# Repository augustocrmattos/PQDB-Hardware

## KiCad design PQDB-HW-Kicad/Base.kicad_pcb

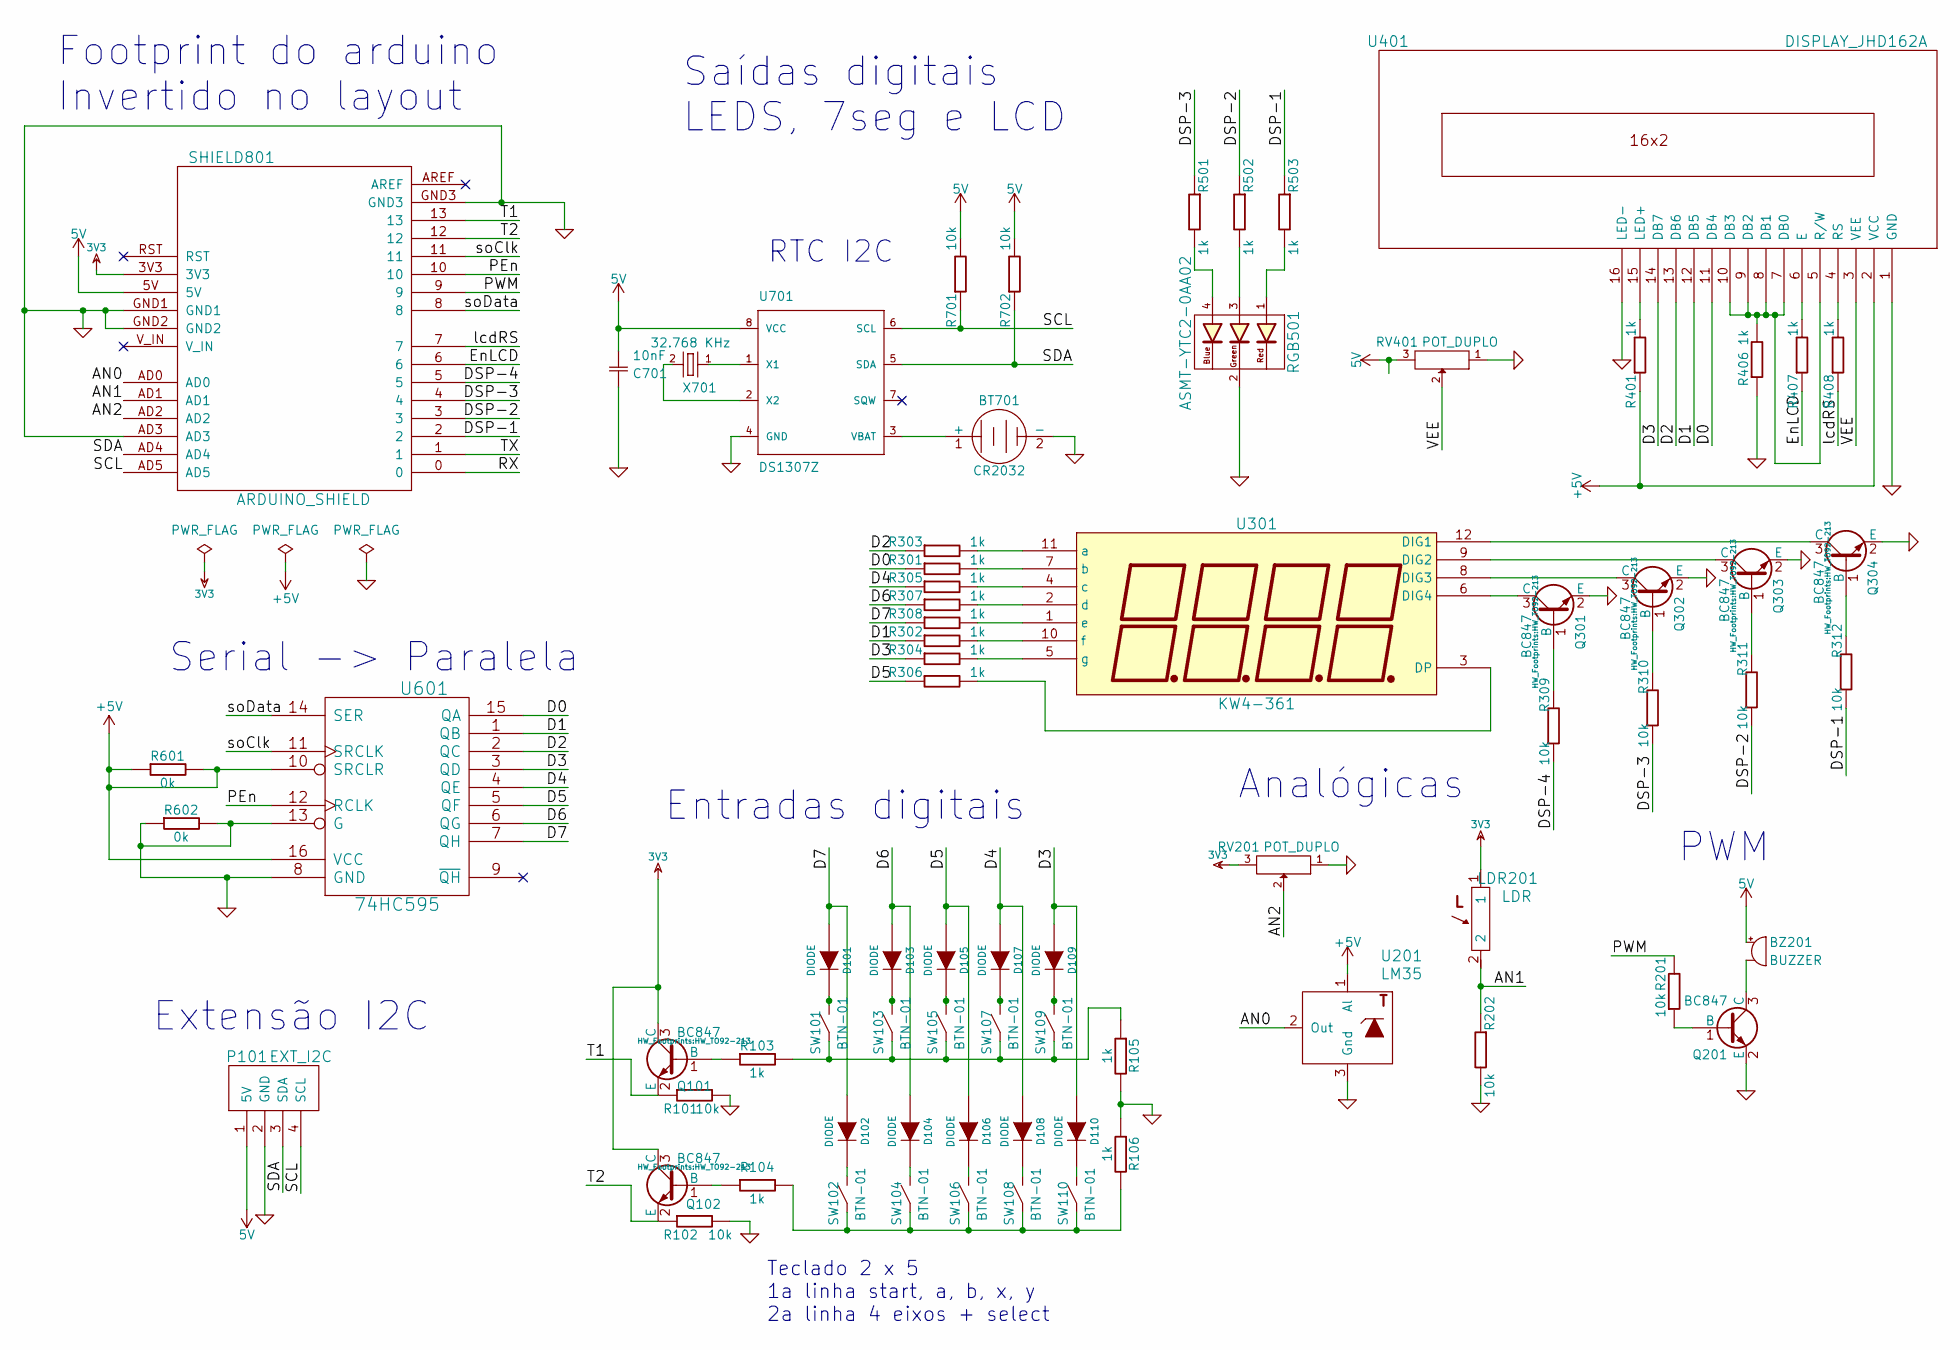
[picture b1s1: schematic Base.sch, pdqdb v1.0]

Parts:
BT701: CR2032; HW_CR2032H
BZ201: BUZZER; HW_Buzzer
C701: 10nF; HW_CAPACITOR
D101, D102, D103, D104, D105, D106, D107, D108, D109, D110: DIODE; D5
LDR201: LDR; HW_LDR
P101: EXT_I2C
Q101, Q102, Q201, Q301, Q302, Q303, Q304: BC847; HW_TO92-213
R101, R102, R201, R202, R309, R310, R311, R312, R701, R702: 10k; HW_Resistor
R103, R104, R105, R106, R301, R302, R303, R304, R305, R306, R307, R308, R401, R406, R407, R408, R501, R502, R503: 1k; HW_Resistor
R601, R602: 0k; Resistor_Horizontal_RM15mm
RGB501: ASMT-YTC2-0AA02; LED-5MM
RV201, RV401: POT_DUPLO; HW_Potenciometro_2_Duplo
SHIELD801: ARDUINO_SHIELD; ARDUINO_SHIELD_2
SW101, SW102, SW103, SW104, SW105, SW106, SW107, SW108, SW109, SW110: BTN-01; HW_Switch_tactil_adaptada
U201: LM35; TO-92_Molded_Narrow_Reverse
U301: KW4-361; HW_Disp_7seg_4dig
U401: DISPLAY_JHD162A; HW_LCD
U601: 74HC595; HW_DIP-16__300_ELL
U701: DS1307Z; DIP-8_W7.62mm_LongPads
X701: 32.768 KHz; Crystal_Round_Horizontal_2mm

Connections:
3V3: LDR201.1, Q101.3 (C), Q102.3 (C), RV201.3, SHIELD801.3V3
/AN0: SHIELD801.AD0, U201.2 (Out)
/AN1: LDR201.2, R202.1, SHIELD801.AD1
/AN2: RV201.2, SHIELD801.AD2
/D0: R301.1, U401.11 (DB4), U601.15 (QA)
/D1: R302.1, U401.12 (DB5), U601.1 (QB)
/D2: R303.1, U401.13 (DB6), U601.2 (QC)
/D3: D109.1 (A), D110.1 (A), R304.1, U401.14 (DB7), U601.3 (QD)
/D4: D107.1 (A), D108.1 (A), R305.1, U601.4 (QE)
/D5: D105.1 (A), D106.1 (A), R306.1, U601.5 (QF)
/D6: D103.1 (A), D104.1 (A), R307.1, U601.6 (QG)
/D7: D101.1 (A), D102.1 (A), R308.1, U601.7 (QH)
/DSP-1: R312.1, R503.1, SHIELD801.2
/DSP-2: R311.1, R502.1, SHIELD801.3
/DSP-3: R310.1, R501.1, SHIELD801.4
/DSP-4: R309.1, SHIELD801.5
/EnLCD: R407.1, SHIELD801.6
/PEn: SHIELD801.10, U601.12 (RCLK)
/PWM: R201.2, SHIELD801.9
/RX: SHIELD801.0
/SCL: P101.4 (SCL), R701.1, SHIELD801.AD5, U701.6 (SCL)
/SDA: P101.3 (SDA), R702.1, SHIELD801.AD4, U701.5 (SDA)
/T1: Q101.2 (E), R101.1, SHIELD801.13
/T2: Q102.2 (E), R102.1, SHIELD801.12
/TX: SHIELD801.1
/VEE: RV401.2, U401.3 (VEE)
/lcdRS: R408.1, SHIELD801.7
/soClk: SHIELD801.11, U601.11 (SRCLK)
/soData: SHIELD801.8, U601.14 (SER)
GND: BT701.2 (-), C701.1, P101.2 (GND), Q201.2 (E), Q301.2 (E), Q302.2 (E), Q303.2 (E), Q304.2 (E), R101.2, R102.2, R105.2, R106.1, R202.2, R406.1, R602.1, R602.2, RGB501.2 (KG), RV201.1, RV401.1, SHIELD801.AD3, SHIELD801.GND1, SHIELD801.GND2, SHIELD801.GND3, U201.3 (Gnd), U401.1 (GND), U401.16 (LED-), U601.8 (GND), U601.13 (G), U701.4 (GND)
unnamed: BT701.1 (+), U701.3 (VBAT)
unnamed: BZ201.2, Q201.3 (C)
unnamed: D101.2 (K), SW101.2
unnamed: D102.2 (K), SW102.2
unnamed: D103.2 (K), SW103.2
unnamed: D104.2 (K), SW104.2
unnamed: D105.2 (K), SW105.2
unnamed: D106.2 (K), SW106.2
unnamed: D107.2 (K), SW107.2
unnamed: D108.2 (K), SW108.2
unnamed: D109.2 (K), SW109.2
unnamed: D110.2 (K), SW110.2
unnamed: Q101.1 (B), R103.1
unnamed: Q102.1 (B), R104.1
unnamed: Q201.1 (B), R201.1
unnamed: Q301.1 (B), R309.2
unnamed: Q301.3 (C), U301.6 (DIG4)
unnamed: Q302.1 (B), R310.2
unnamed: Q302.3 (C), U301.8 (DIG3)
unnamed: Q303.1 (B), R311.2
unnamed: Q303.3 (C), U301.9 (DIG2)
unnamed: Q304.1 (B), R312.2
unnamed: Q304.3 (C), U301.12 (DIG1)
unnamed: R103.2, R105.1, SW101.1, SW103.1, SW105.1, SW107.1, SW109.1
unnamed: R104.2, R106.2, SW102.1, SW104.1, SW106.1, SW108.1, SW110.1
unnamed: R301.2, U301.7 (b)
unnamed: R302.2, U301.10 (f)
unnamed: R303.2, U301.11 (a)
unnamed: R304.2, U301.5 (g)
unnamed: R305.2, U301.4 (c)
unnamed: R306.2, U301.3 (DP)
unnamed: R307.2, U301.2 (d)
unnamed: R308.2, U301.1 (e)
unnamed: R401.2, U401.15 (LED+)
unnamed: R406.2, U401.5 (R/W), U401.7 (DB0), U401.8 (DB1), U401.9 (DB2), U401.10 (DB3)
unnamed: R407.2, U401.6 (E)
unnamed: R408.2, U401.4 (RS)
unnamed: R501.2, RGB501.4 (AB)
unnamed: R502.2, RGB501.3 (AG)
unnamed: R503.2, RGB501.1 (AR)
unnamed: U701.1 (X1), X701.1
unnamed: U701.2 (X2), X701.2

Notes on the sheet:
RTC I2C
Saídas digitais LEDS, 7seg e LCD
Teclado 2 x 5 1a linha start, a, b, x, y 2a linha 4 eixos + select
Analógicas
PWM
Serial -> Paralela
Footprint do arduino Invertido no layout
Entradas digitais
Extensão I2C

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
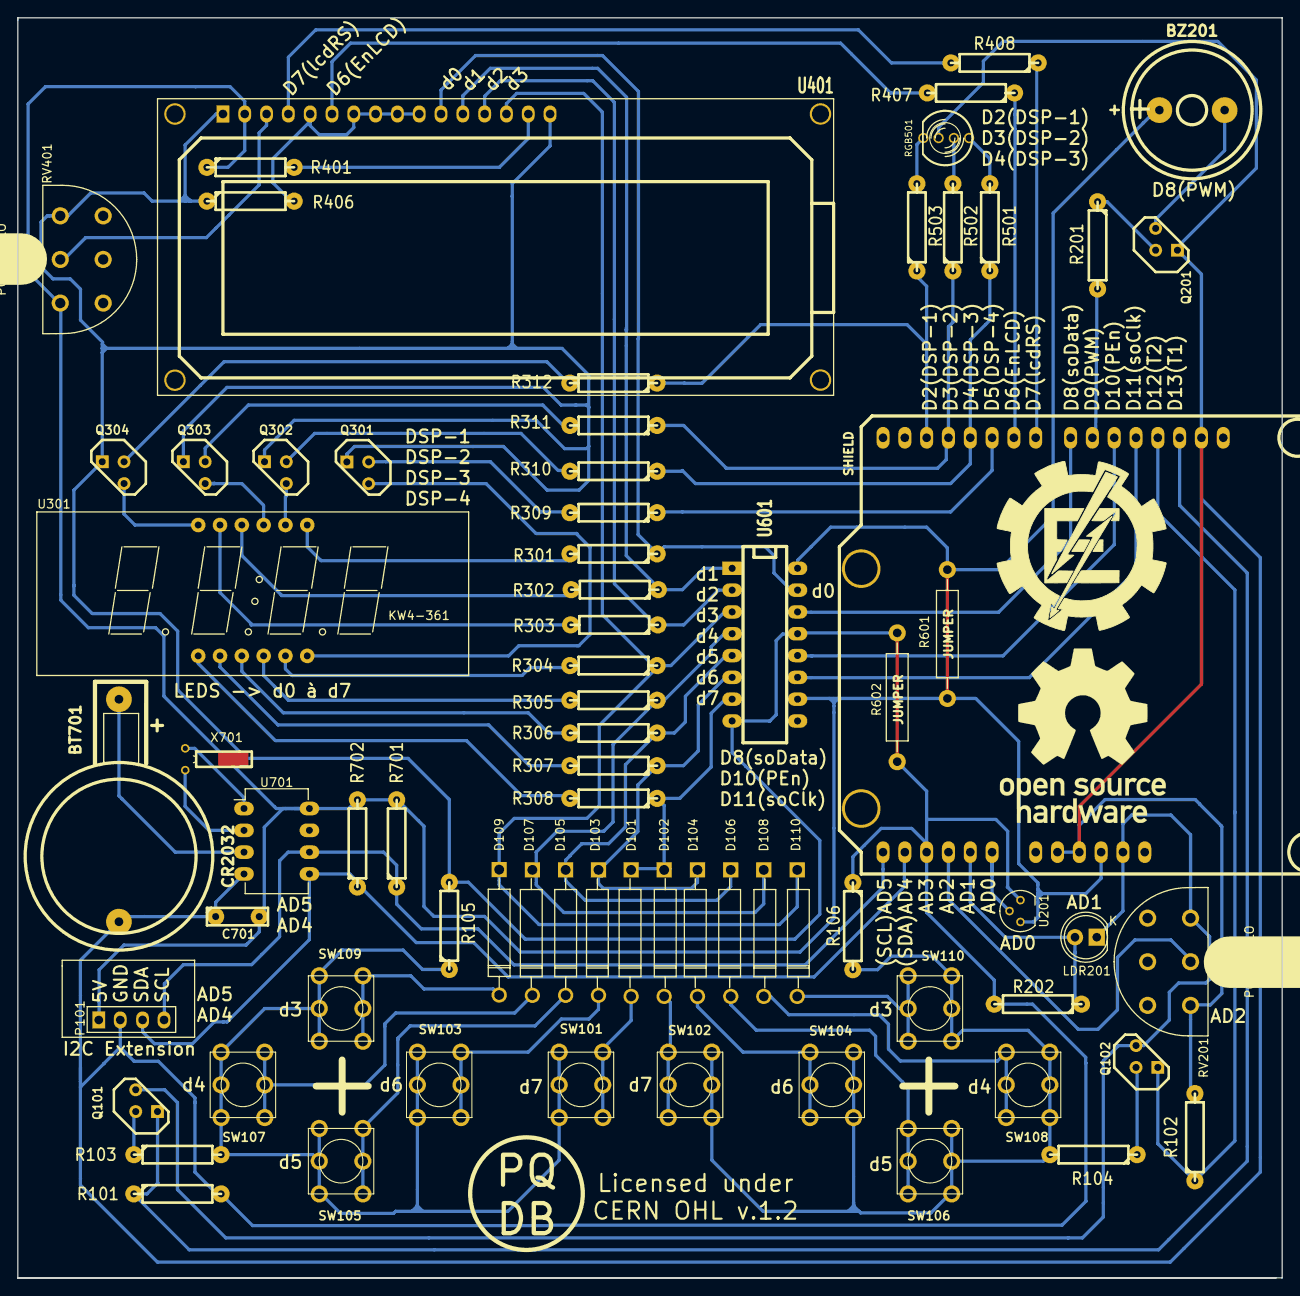
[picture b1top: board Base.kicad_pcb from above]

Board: 2 copper layers, 147.2 x 146.8 mm, 73 parts (1 on the bottom side), 71 nets.

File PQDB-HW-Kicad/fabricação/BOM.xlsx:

Reference | Value | Footprint
R312 | Resistor 1/8W 10K PTH | CR25
R201 | Resistor 1/8W 10K PTH | CR25
R311 | Resistor 1/8W 10K PTH | CR25
R310 | Resistor 1/8W 10K PTH | CR25
R309 | Resistor 1/8W 10K PTH | CR25
R202 | Resistor 1/8W 10K PTH | CR25
R102 | Resistor 1/8W 10K PTH | CR25
R701 | Resistor 1/8W 10K PTH | CR25
R702 | Resistor 1/8W 10K PTH | CR25
R101 | Resistor 1/8W 10K PTH | CR25
C701 | Capacitor cerâmico 25V 10nF PTH | 5mm
R407 | Resistor 1/8W 1K PTH | CR25
R408 | Resistor 1/8W 1K PTH | CR25
R406 | Resistor 1/8W 1K PTH | CR25
R304 | Resistor 1/8W 1K PTH | CR25
R303 | Resistor 1/8W 1K PTH | CR25
R302 | Resistor 1/8W 1K PTH | CR25
R301 | Resistor 1/8W 1K PTH | CR25
R308 | Resistor 1/8W 1K PTH | CR25
R307 | Resistor 1/8W 1K PTH | CR25
R306 | Resistor 1/8W 1K PTH | CR25
R305 | Resistor 1/8W 1K PTH | CR25
R401 | Resistor 1/8W 1K PTH | CR25
R501 | Resistor 1/8W 1K PTH | CR25
R502 | Resistor 1/8W 1K PTH | CR25
R503 | Resistor 1/8W 1K PTH | CR25
R103 | Resistor 1/8W 1K PTH | CR25
R105 | Resistor 1/8W 1K PTH | CR25
R106 | Resistor 1/8W 1K PTH | CR25
R104 | Resistor 1/8W 1K PTH | CR25
X701 | Cristal Axial 32,768 KHz | TC2x6
U601 | 74HC595 | DIP-16
RGB501 | LED RGB 5mm | 4 Pinos
Q304 | BC547 | TO-92
Q303 | BC547 | TO-92
Q302 | BC547 | TO-92
Q301 | BC547 | TO-92
Q201 | BC547 | TO-92
Q101 | BC547 | TO-92
Q102 | BC547 | TO-92
SW103 | Chave Tactil 6x6x4,3 180 graus 4 Terminais PTH | 6x6x4,3mm
SW105 | Chave Tactil 6x6x4,3 180 graus 4 Terminais PTH | 6x6x4,3mm
SW107 | Chave Tactil 6x6x4,3 180 graus 4 Terminais PTH | 6x6x4,3mm
SW109 | Chave Tactil 6x6x4,3 180 graus 4 Terminais PTH | 6x6x4,3mm
SW101 | Chave Tactil 6x6x4,3 180 graus 4 Terminais PTH | 6x6x4,3mm
SW104 | Chave Tactil 6x6x4,3 180 graus 4 Terminais PTH | 6x6x4,3mm
SW106 | Chave Tactil 6x6x4,3 180 graus 4 Terminais PTH | 6x6x4,3mm
SW108 | Chave Tactil 6x6x4,3 180 graus 4 Terminais PTH | 6x6x4,3mm
SW110 | Chave Tactil 6x6x4,3 180 graus 4 Terminais PTH | 6x6x4,3mm
SW102 | Chave Tactil 6x6x4,3 180 graus 4 Terminais PTH | 6x6x4,3mm
BZ201 | Buzzer 5V | Espaçamento 7,6mm
BT701 | Suporte para bateria CR2032
D101 | 1N4148 | DO-35
D103 | 1N4148 | DO-35
D105 | 1N4148 | DO-35
D107 | 1N4148 | DO-35
D109 | 1N4148 | DO-35
D102 | 1N4148 | DO-35
D104 | 1N4148 | DO-35
D106 | 1N4148 | DO-35
D108 | 1N4148 | DO-35
D110 | 1N4148 | DO-35
U401 | DISPLAY LCD JHD162A
U701 | DS1307Z | DIP-8
U301 | Display 7 segmentos 4 digitos KW4-361
LDR201 | LDR 5mm 2 terminais
U201 | LM35 | TO-92
RV401 | Potenciômetro duplo 10K | Espaçamento 5mm
RV201 | Potenciômetro duplo 10K | Espaçamento 5mm
SHIELD801 | Barra de pinos 1x40 20mm | Espaçamento 2,54mm

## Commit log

2017-10-26 Create teste
2017-10-26 Create walter
2017-10-26 Create a
2018-05-15 Silk screen update
    Corrigida referencia do silk nos botões.
    Adiçào das referências dos componentes na camada de silk.

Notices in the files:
PQDB-HW-Kicad/Base.kicad_pcb:
Licensed under
CERN OHL v.1.2
PQDB-HW-Kicad/Base.sch:
Licensed under CERN OHL v.1.2
